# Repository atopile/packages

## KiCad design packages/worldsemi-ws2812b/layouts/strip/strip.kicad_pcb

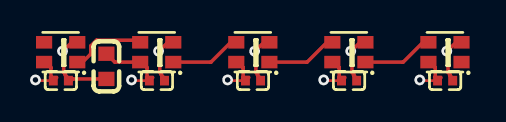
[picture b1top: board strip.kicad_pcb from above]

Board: 2 copper layers, 11 parts (0 on the bottom side), 6 nets.

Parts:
C1: 10µF ±10%; C0603
C2, C3, C4, C5, C6: 100nF ±10%; C0402
LED1, LED2, LED3, LED4, LED5: LED-SMD_4P-L2.0-W2.0-TL_WS2812B-2020

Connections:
hv: C1.1, C2.1, C3.1, C4.1, C5.1, C6.1, LED1.4, LED2.4, LED3.4, LED4.4, LED5.4
leds[1]-data_in-DI: LED1.1, LED2.3
leds[2]-data_in-DI: LED2.1, LED3.3
leds[3]-data_in-DI: LED3.1, LED4.3
leds[4]-data_in-DI: LED4.1, LED5.3
lv: C1.2, C2.2, C3.2, C4.2, C5.2, C6.2, LED1.2, LED2.2, LED3.2, LED4.2, LED5.2

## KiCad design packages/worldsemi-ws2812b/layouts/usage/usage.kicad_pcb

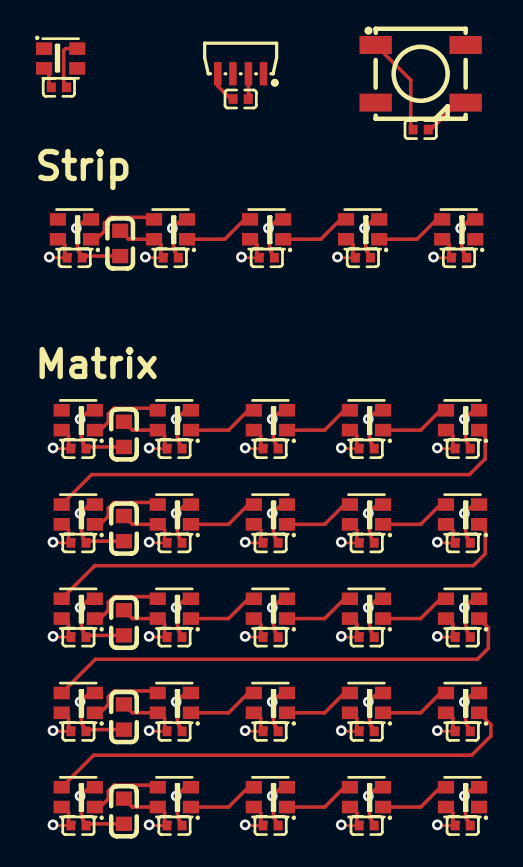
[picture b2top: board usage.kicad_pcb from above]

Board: 2 copper layers, 72 parts (0 on the bottom side), 32 nets.

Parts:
C1, C2, C3, C14, C15, C16, C17, C18, C20, C21, C22, C23, C24, C26, C27, C28, C29, C30, C32, C33, C34, C35, C36, C38, C39, C40, C41, C42, C44, C45, C46, C47, C48: 100nF ±10%; C0402
C13, C19, C25, C31, C37, C43: 10µF ±10%; C0603
LED1, LED13, LED14, LED15, LED16, LED17, LED18, LED19, LED20, LED21, LED22, LED23, LED24, LED25, LED26, LED27, LED28, LED29, LED30, LED31, LED32, LED33, LED34, LED35, LED36, LED37, LED38, LED39, LED40, LED41, LED42: LED-SMD_4P-L2.0-W2.0-TL_WS2812B-2020
LED2: LED-SMD_WS2812B-4020
LED3: LED-SMD_4P-L5.0-W5.0-TL-1

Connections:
1: LED1.1, LED2.1
DI: LED13.1, LED14.3
DIN: LED2.3, LED3.4
hv: C1.1, C2.1, C3.1, C13.1, C14.1, C15.1, C16.1, C17.1, C18.1, C19.1, C20.1, C21.1, C22.1, C23.1, C24.1, C25.1, C26.1, C27.1, C28.1, C29.1, C30.1, C31.1, C32.1, C33.1, C34.1, C35.1, C36.1, C37.1, C38.1, C39.1, C40.1, C41.1, C42.1, C43.1, C44.1, C45.1, C46.1, C47.1, C48.1, LED1.4, LED2.2, LED3.1, LED13.4, LED14.4, LED15.4, LED16.4, LED17.4, LED18.4, LED19.4, LED20.4, LED21.4, LED22.4, LED23.4, LED24.4, LED25.4, LED26.4, LED27.4, LED28.4, LED29.4, LED30.4, LED31.4, LED32.4, LED33.4, LED34.4, LED35.4, LED36.4, LED37.4, LED38.4, LED39.4, LED40.4, LED41.4, LED42.4
leds[1]-data_in-DI: LED18.1, LED19.3
leds[1]-data_in-DI-1: LED23.1, LED24.3
leds[1]-data_in-DI-2: LED28.1, LED29.3
leds[1]-data_in-DI-3: LED33.1, LED34.3
leds[1]-data_in-DI-4: LED38.1, LED39.3
leds[2]-data_in-DI: LED14.1, LED15.3
leds[2]-data_in-DI-1: LED19.1, LED20.3
leds[2]-data_in-DI-2: LED24.1, LED25.3
leds[2]-data_in-DI-3: LED29.1, LED30.3
leds[2]-data_in-DI-4: LED34.1, LED35.3
leds[2]-data_in-DI-5: LED39.1, LED40.3
leds[3]-data_in-DI: LED15.1, LED16.3
leds[3]-data_in-DI-1: LED20.1, LED21.3
leds[3]-data_in-DI-2: LED25.1, LED26.3
leds[3]-data_in-DI-3: LED30.1, LED31.3
leds[3]-data_in-DI-4: LED35.1, LED36.3
leds[3]-data_in-DI-5: LED40.1, LED41.3
leds[4]-data_in-DI: LED16.1, LED17.3
leds[4]-data_in-DI-1: LED21.1, LED22.3
leds[4]-data_in-DI-2: LED26.1, LED27.3
leds[4]-data_in-DI-3: LED31.1, LED32.3
leds[4]-data_in-DI-4: LED36.1, LED37.3
leds[4]-data_in-DI-5: LED41.1, LED42.3
lv: C1.2, C2.2, C3.2, C13.2, C14.2, C15.2, C16.2, C17.2, C18.2, C19.2, C20.2, C21.2, C22.2, C23.2, C24.2, C25.2, C26.2, C27.2, C28.2, C29.2, C30.2, C31.2, C32.2, C33.2, C34.2, C35.2, C36.2, C37.2, C38.2, C39.2, C40.2, C41.2, C42.2, C43.2, C44.2, C45.2, C46.2, C47.2, C48.2, LED1.2, LED2.4, LED3.3, LED13.2, LED14.2, LED15.2, LED16.2, LED17.2, LED18.2, LED19.2, LED20.2, LED21.2, LED22.2, LED23.2, LED24.2, LED25.2, LED26.2, LED27.2, LED28.2, LED29.2, LED30.2, LED31.2, LED32.2, LED33.2, LED34.2, LED35.2, LED36.2, LED37.2, LED38.2, LED39.2, LED40.2, LED41.2, LED42.2
strips[1]-data_in-line: LED22.1, LED23.3
strips[2]-data_in-line: LED27.1, LED28.3
strips[3]-data_in-line: LED32.1, LED33.3
strips[4]-data_in-line: LED37.1, LED38.3

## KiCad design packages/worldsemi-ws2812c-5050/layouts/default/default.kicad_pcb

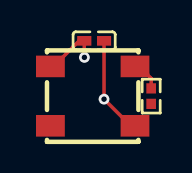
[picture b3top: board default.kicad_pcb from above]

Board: 2 copper layers, 3 parts (0 on the bottom side), 3 nets.

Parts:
C1: 100nF ±10% 16V X7R; C0402
LED1: LED-SMD_4P-L5.0-W5.0-LS5.4-TL-1
R1: 330Ω ±1% 62.5mW; R0402

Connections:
DIN: LED1.4, R1.2
GND: C1.2, LED1.3
VCC: C1.1, LED1.1

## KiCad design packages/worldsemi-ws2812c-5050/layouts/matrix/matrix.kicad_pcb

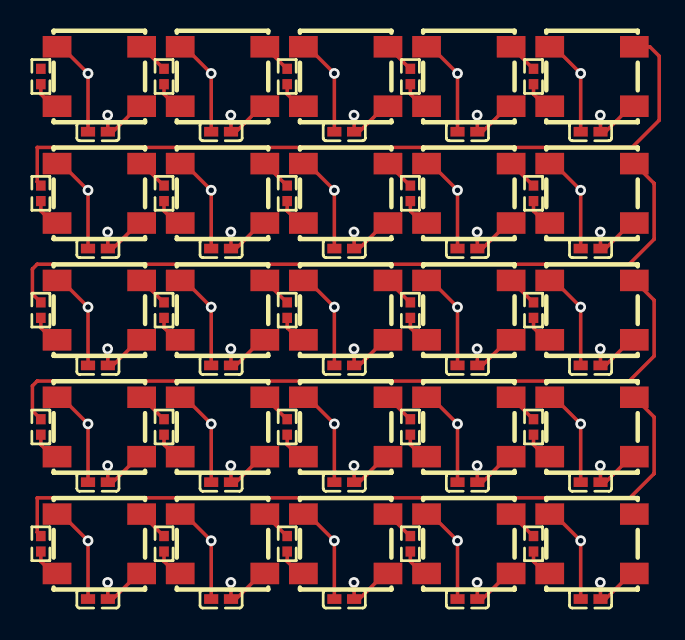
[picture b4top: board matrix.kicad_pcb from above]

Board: 2 copper layers, 75 parts (0 on the bottom side), 51 nets.

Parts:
C2, C3, C4, C5, C6, C13, C14, C15, C16, C17, C24, C25, C26, C27, C28, C35, C36, C37, C38, C39, C46, C47, C48, C49, C50: 100nF ±10% 16V X7R; C0402
LED1, LED2, LED3, LED4, LED5, LED11, LED12, LED13, LED14, LED15, LED21, LED22, LED23, LED24, LED25, LED31, LED32, LED33, LED34, LED35, LED41, LED42, LED43, LED44, LED45: LED-SMD_4P-L5.0-W5.0-LS5.4-TL-1
R1, R2, R3, R4, R5, R11, R12, R13, R14, R15, R21, R22, R23, R24, R25, R31, R32, R33, R34, R35, R41, R42, R43, R44, R45: 330Ω ±1% 62.5mW; R0402

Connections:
GND: C2.2, C3.2, C4.2, C5.2, C6.2, C13.2, C14.2, C15.2, C16.2, C17.2, C24.2, C25.2, C26.2, C27.2, C28.2, C35.2, C36.2, C37.2, C38.2, C39.2, C46.2, C47.2, C48.2, C49.2, C50.2, LED1.3, LED2.3, LED3.3, LED4.3, LED5.3, LED11.3, LED12.3, LED13.3, LED14.3, LED15.3, LED21.3, LED22.3, LED23.3, LED24.3, LED25.3, LED31.3, LED32.3, LED33.3, LED34.3, LED35.3, LED41.3, LED42.3, LED43.3, LED44.3, LED45.3
VCC: C2.1, C3.1, C4.1, C5.1, C6.1, C13.1, C14.1, C15.1, C16.1, C17.1, C24.1, C25.1, C26.1, C27.1, C28.1, C35.1, C36.1, C37.1, C38.1, C39.1, C46.1, C47.1, C48.1, C49.1, C50.1, LED1.1, LED2.1, LED3.1, LED4.1, LED5.1, LED11.1, LED12.1, LED13.1, LED14.1, LED15.1, LED21.1, LED22.1, LED23.1, LED24.1, LED25.1, LED31.1, LED32.1, LED33.1, LED34.1, LED35.1, LED41.1, LED42.1, LED43.1, LED44.1, LED45.1
data_protection_r-DIN-0: LED1.4, R1.2
data_protection_r-DIN-1: LED2.4, R2.2
data_protection_r-DIN-2: LED3.4, R3.2
data_protection_r-DIN-3: LED4.4, R4.2
data_protection_r-DIN-4: LED5.4, R5.2
data_protection_r-DIN-5: LED11.4, R11.2
data_protection_r-DIN-6: LED12.4, R12.2
data_protection_r-DIN-7: LED13.4, R13.2
data_protection_r-DIN-8: LED14.4, R14.2
data_protection_r-DIN-9: LED15.4, R15.2
data_protection_r-DIN-10: LED21.4, R21.2
data_protection_r-DIN-11: LED22.4, R22.2
data_protection_r-DIN-12: LED23.4, R23.2
data_protection_r-DIN-13: LED24.4, R24.2
data_protection_r-DIN-14: LED25.4, R25.2
data_protection_r-DIN-15: LED31.4, R31.2
data_protection_r-DIN-16: LED32.4, R32.2
data_protection_r-DIN-17: LED33.4, R33.2
data_protection_r-DIN-18: LED34.4, R34.2
data_protection_r-DIN-19: LED35.4, R35.2
data_protection_r-DIN-20: LED41.4, R41.2
data_protection_r-DIN-21: LED42.4, R42.2
data_protection_r-DIN-22: LED43.4, R43.2
data_protection_r-DIN-23: LED44.4, R44.2
data_protection_r-DIN-24: LED45.4, R45.2
leds[1]-data_in-DOUT-0: LED1.2, R2.1
leds[1]-data_in-DOUT-1: LED11.2, R12.1
leds[1]-data_in-DOUT-2: LED21.2, R22.1
leds[1]-data_in-DOUT-3: LED31.2, R32.1
leds[1]-data_in-DOUT-4: LED41.2, R42.1
leds[2]-data_in-DOUT-0: LED2.2, R3.1
leds[2]-data_in-DOUT-1: LED12.2, R13.1
leds[2]-data_in-DOUT-2: LED22.2, R23.1
leds[2]-data_in-DOUT-3: LED32.2, R33.1
leds[2]-data_in-DOUT-4: LED42.2, R43.1
leds[3]-data_in-DOUT-0: LED3.2, R4.1
leds[3]-data_in-DOUT-1: LED13.2, R14.1
leds[3]-data_in-DOUT-2: LED23.2, R24.1
leds[3]-data_in-DOUT-3: LED33.2, R34.1
leds[3]-data_in-DOUT-4: LED43.2, R44.1
leds[4]-data_in-DOUT-0: LED4.2, R5.1
leds[4]-data_in-DOUT-1: LED14.2, R15.1
leds[4]-data_in-DOUT-2: LED24.2, R25.1
leds[4]-data_in-DOUT-3: LED34.2, R35.1
leds[4]-data_in-DOUT-4: LED44.2, R45.1
strips[1]-data_in-line: LED5.2, R11.1
strips[2]-data_in-line: LED15.2, R21.1
strips[3]-data_in-line: LED25.2, R31.1
strips[4]-data_in-line: LED35.2, R41.1
